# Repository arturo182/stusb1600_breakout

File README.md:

# STUSB1600 USB Type-C Controller Breakout Board

A breakout board for the STUSB1600 USB Type-C controller, with PMOD-ish connector.

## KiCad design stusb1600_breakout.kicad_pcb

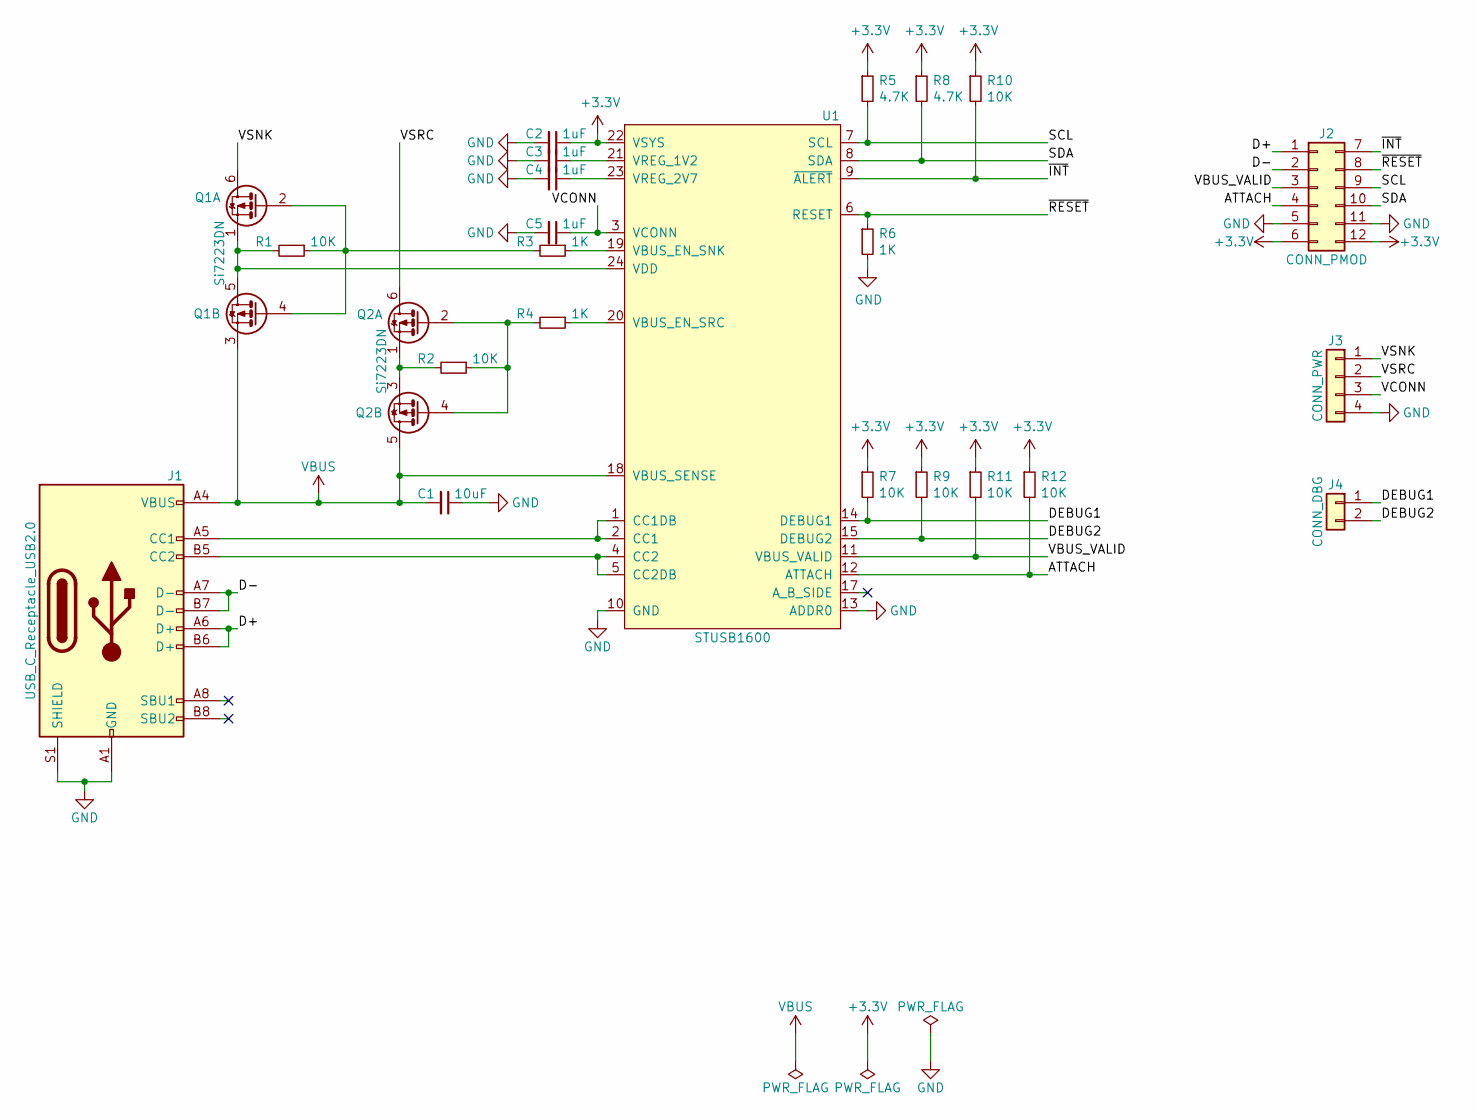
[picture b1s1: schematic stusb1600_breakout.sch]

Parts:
C1: 10uF; C_0603_1608Metric
C2, C3, C4, C5: 1uF; C_0603_1608Metric
J1: USB_C_Receptacle_USB2.0; USB_C_Receptacle_GT-USB-7010
J2: CONN_PMOD; PMODHeader_2x06_P2.54mm_Horizontal
J3: CONN_PWR; PinHeader_1x04_P2.54mm_Vertical
J4: CONN_DBG; PinHeader_1x02_P2.54mm_Vertical
Q1, Q2: Si7223DN; Vishay_PowerPAK_1212-8_Dual
R1, R2, R7, R9, R10, R11, R12: 10K; R_0402_1005Metric
R3, R4, R6: 1K; R_0402_1005Metric
R5, R8: 4.7K; R_0402_1005Metric
U1: STUSB1600; QFN-24-1EP_4x4mm_P0.5mm_EP2.7x2.7mm

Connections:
+3V3: C2.1, J2.6, J2.12, R5.1, R7.1, R8.1, R9.1, R10.1, R11.1, R12.1, U1.22 (VSYS)
/ATTACH: J2.4, R12.2, U1.12 (ATTACH)
/D+: J1.A6 (D+), J1.B6 (D+), J2.1
/D-: J1.A7 (D-), J1.B7 (D-), J2.2
/DEBUG1: J4.1, R7.2, U1.14 (DEBUG1)
/DEBUG2: J4.2, R9.2, U1.15 (DEBUG2)
/SCL: J2.9, R5.2, U1.7 (SCL)
/SDA: J2.10, R8.2, U1.8 (SDA)
/VBUS_VALID: J2.3, R11.2, U1.11 (VBUS_VALID)
/VCONN: C5.1, J3.3, U1.3 (VCONN)
/VSNK: J3.1, Q1.6 (D1)
/VSRC: J3.2, Q2.6 (D1)
/~INT~: J2.7, R10.2, U1.9 (~ALERT~)
/~RESET~: J2.8, R6.1, U1.6 (RESET)
GND: C1.1, C2.2, C3.2, C4.2, C5.2, J1.A1 (GND), J1.A12 (GND), J1.B1 (GND), J1.B12 (GND), J1.S1 (SHIELD), J2.5, J2.11, J3.4, R6.2, U1.10 (GND), U1.13 (ADDR0), U1.25 (GND)
unnamed: C3.1, U1.21 (VREG_1V2)
unnamed: C4.1, U1.23 (VREG_2V7)
unnamed: J1.A5 (CC1), U1.1 (CC1DB), U1.2 (CC1)
unnamed: J1.B5 (CC2), U1.4 (CC2), U1.5 (CC2DB)
unnamed: Q1.1 (S1), Q1.5 (D2), R1.2, U1.24 (VDD)
unnamed: Q1.2 (G1), Q1.4 (G2), R1.1, R3.2
unnamed: Q2.1 (S1), Q2.3 (S2), R2.2
unnamed: Q2.2 (G1), Q2.4 (G2), R2.1, R4.2
unnamed: R3.1, U1.19 (VBUS_EN_SNK)
unnamed: R4.1, U1.20 (VBUS_EN_SRC)
VBUS: C1.2, J1.A4 (VBUS), J1.A9 (VBUS), J1.B4 (VBUS), J1.B9 (VBUS), Q1.3 (S2), Q2.5 (D2), U1.18 (VBUS_SENSE)

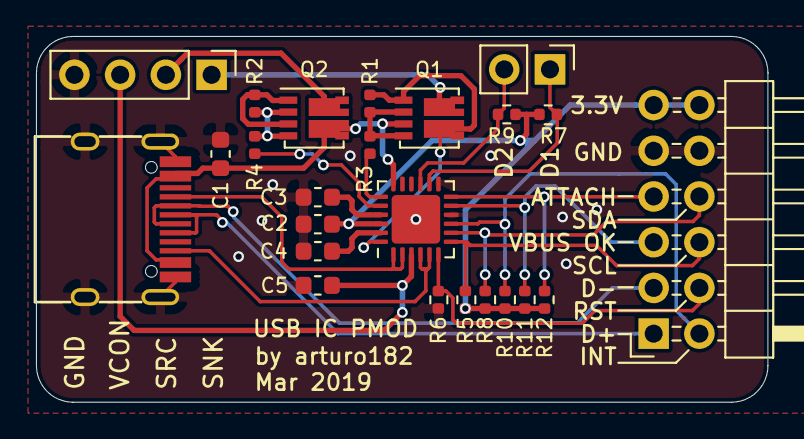
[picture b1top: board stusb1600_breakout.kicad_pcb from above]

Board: 2 copper layers, 40.6 x 20.3 mm, 24 parts (0 on the bottom side), 26 nets.

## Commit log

2019-05-02 Initial import
2019-05-12 Add schematics, BOM, images and update README
